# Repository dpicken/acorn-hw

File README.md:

# acorn-hw

Hardware for Acorn RISC OS computers.

- [A3010 SysClk Switcher](/doc/a3010-sysclk-switcher.md)

- [A3010 4 MiB RAM Upgrade](/doc/a3010-ram-upgrade.md)

- [Acorn USB Mouse](/doc/usb-mouse.md)

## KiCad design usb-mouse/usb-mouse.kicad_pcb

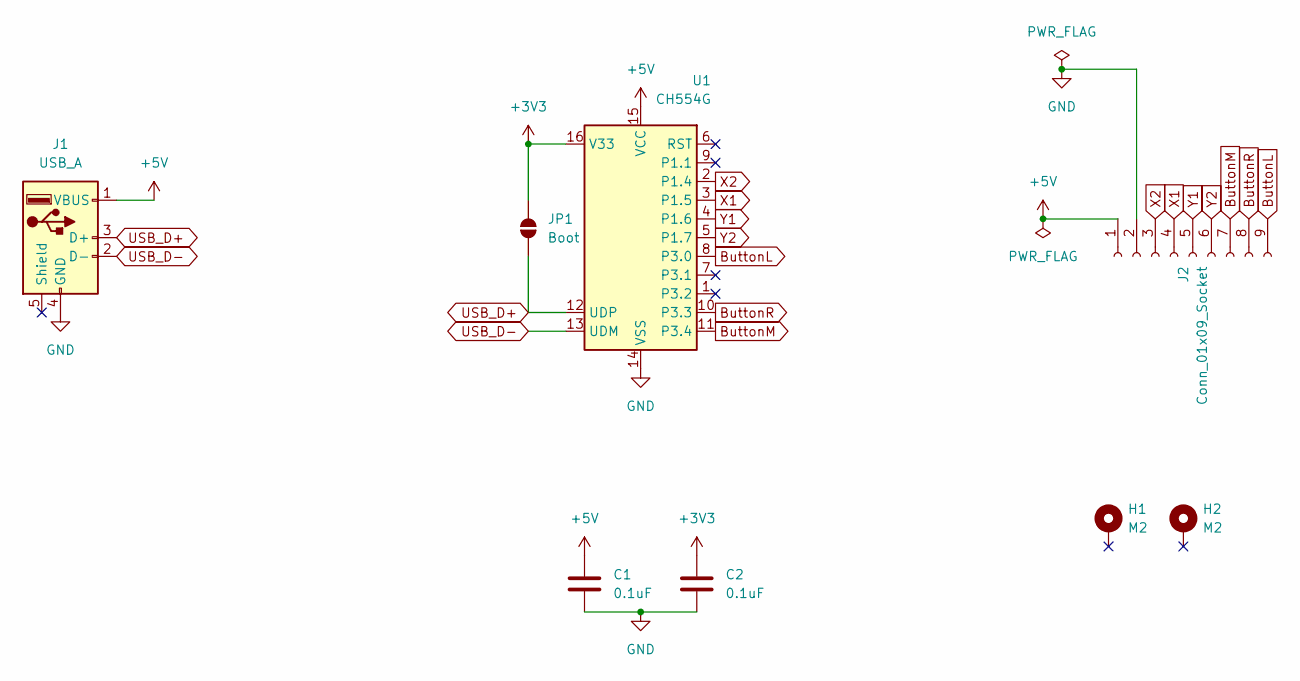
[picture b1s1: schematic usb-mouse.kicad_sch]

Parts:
C1, C2: 0.1uF; C_0805_2012Metric_Pad1.18x1.45mm_HandSolder
H1, H2: M2; MountingHole_2.2mm_M2_DIN965_Pad
J1: USB_A; USB_A_Molex_67643_Horizontal
J2: Conn_01x09_Socket; PinHeader_1x09_P1.27mm_Vertical
JP1: Boot; SolderJumper-2_P1.3mm_Open_RoundedPad1.0x1.5mm
U1: CH554G; STC_SOP-16_3.9x9.9mm_P1.27mm

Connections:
+3V3: C2.1, JP1.1 (A), U1.16 (V33)
+5V: C1.1, J1.1 (VBUS), J2.1, U1.15 (VCC)
ButtonL: J2.9, U1.8 (P3.0)
ButtonM: J2.7, U1.11 (P3.4)
ButtonR: J2.8, U1.10 (P3.3)
GND: C1.2, C2.2, J1.4 (GND), J2.2, U1.14 (VSS)
USB_D+: J1.3 (D+), JP1.2 (B), U1.12 (UDP)
USB_D-: J1.2 (D-), U1.13 (UDM)
X1: J2.4, U1.3 (P1.5)
X2: J2.3, U1.2 (P1.4)
Y1: J2.5, U1.4 (P1.6)
Y2: J2.6, U1.5 (P1.7)

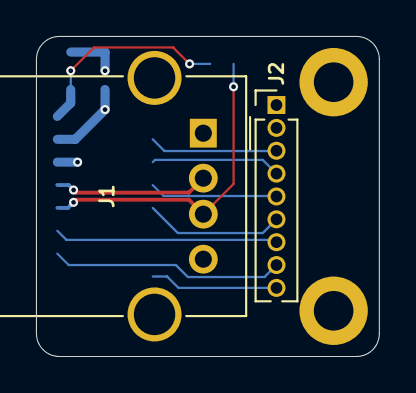
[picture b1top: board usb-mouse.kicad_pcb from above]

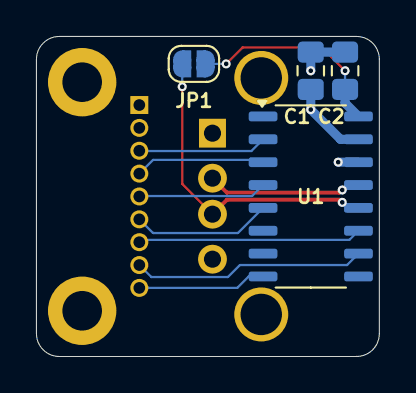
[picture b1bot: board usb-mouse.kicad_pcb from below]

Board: 4 copper layers, 19.1 x 17.8 mm, 8 parts (4 on the bottom side), 12 nets.

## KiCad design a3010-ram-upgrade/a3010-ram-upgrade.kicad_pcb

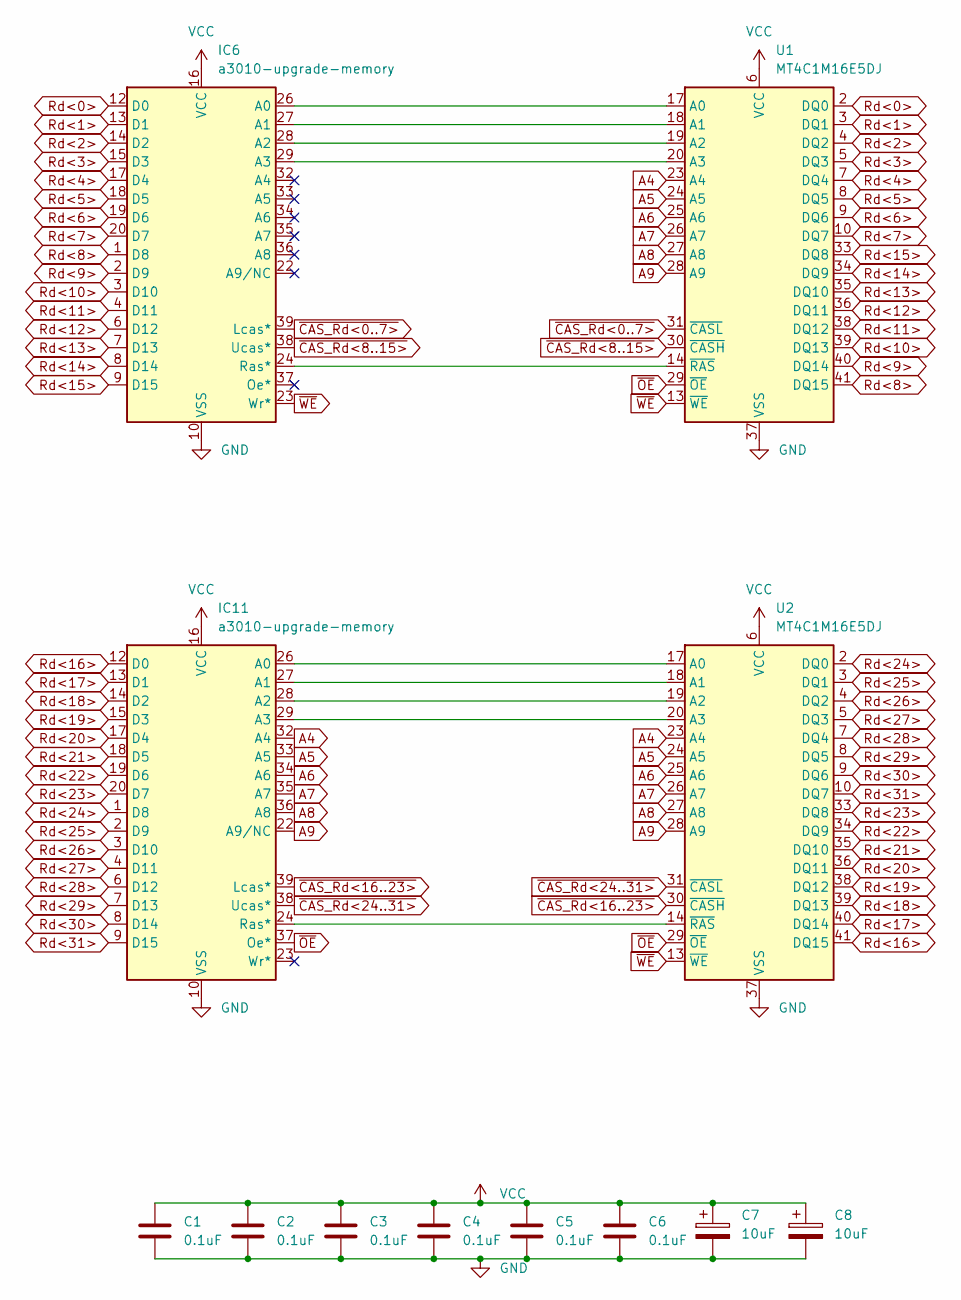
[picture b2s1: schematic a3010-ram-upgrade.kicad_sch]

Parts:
C1, C2, C3, C4, C5, C6: 0.1uF; C_0805_2012Metric_Pad1.18x1.45mm_HandSolder
C7, C8: 10uF; CP_EIA-2012-12_Kemet-R_HandSolder
IC6, IC11: a3010-upgrade-memory; zip-40
U1, U2: MT4C1M16E5DJ; SOJ-42_10.16x26.035mm_P1.27mm

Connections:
A4: IC11.32 (A4), U1.23 (A4), U2.23 (A4)
A5: IC11.33 (A5), U1.24 (A5), U2.24 (A5)
A6: IC11.34 (A6), U1.25 (A6), U2.25 (A6)
A7: IC11.35 (A7), U1.26 (A7), U2.26 (A7)
A8: IC11.36 (A8), U1.27 (A8), U2.27 (A8)
A9: IC11.22 (A9/NC), U1.28 (A9), U2.28 (A9)
GND: C1.2, C2.2, C3.2, C4.2, C5.2, C6.2, C7.2, C8.2, IC6.5 (VSS), IC6.10 (VSS), IC6.31 (VSS), IC11.5 (VSS), IC11.10 (VSS), IC11.31 (VSS), U1.22 (VSS), U1.37 (VSS), U1.42 (VSS), U2.22 (VSS), U2.37 (VSS), U2.42 (VSS)
unnamed: IC6.26 (A0), U1.17 (A0)
unnamed: IC6.27 (A1), U1.18 (A1)
unnamed: IC6.28 (A2), U1.19 (A2)
unnamed: IC6.29 (A3), U1.20 (A3)
unnamed: IC6.24 (Ras*), U1.14 (~RAS)
unnamed: IC11.26 (A0), U2.17 (A0)
unnamed: IC11.27 (A1), U2.18 (A1)
unnamed: IC11.28 (A2), U2.19 (A2)
unnamed: IC11.29 (A3), U2.20 (A3)
unnamed: IC11.24 (Ras*), U2.14 (~RAS)
Rd<0>: IC6.12 (D0), U1.2 (DQ0)
Rd<1>: IC6.13 (D1), U1.3 (DQ1)
Rd<2>: IC6.14 (D2), U1.4 (DQ2)
Rd<3>: IC6.15 (D3), U1.5 (DQ3)
Rd<4>: IC6.17 (D4), U1.7 (DQ4)
Rd<5>: IC6.18 (D5), U1.8 (DQ5)
Rd<6>: IC6.19 (D6), U1.9 (DQ6)
Rd<7>: IC6.20 (D7), U1.10 (DQ7)
Rd<8>: IC6.1 (D8), U1.41 (DQ15)
Rd<9>: IC6.2 (D9), U1.40 (DQ14)
Rd<10>: IC6.3 (D10), U1.39 (DQ13)
Rd<11>: IC6.4 (D11), U1.38 (DQ12)
Rd<12>: IC6.6 (D12), U1.36 (DQ11)
Rd<13>: IC6.7 (D13), U1.35 (DQ10)
Rd<14>: IC6.8 (D14), U1.34 (DQ9)
Rd<15>: IC6.9 (D15), U1.33 (DQ8)
Rd<16>: IC11.12 (D0), U2.41 (DQ15)
Rd<17>: IC11.13 (D1), U2.40 (DQ14)
Rd<18>: IC11.14 (D2), U2.39 (DQ13)
Rd<19>: IC11.15 (D3), U2.38 (DQ12)
Rd<20>: IC11.17 (D4), U2.36 (DQ11)
Rd<21>: IC11.18 (D5), U2.35 (DQ10)
Rd<22>: IC11.19 (D6), U2.34 (DQ9)
Rd<23>: IC11.20 (D7), U2.33 (DQ8)
Rd<24>: IC11.1 (D8), U2.2 (DQ0)
Rd<25>: IC11.2 (D9), U2.3 (DQ1)
Rd<26>: IC11.3 (D10), U2.4 (DQ2)
Rd<27>: IC11.4 (D11), U2.5 (DQ3)
Rd<28>: IC11.6 (D12), U2.7 (DQ4)
Rd<29>: IC11.7 (D13), U2.8 (DQ5)
Rd<30>: IC11.8 (D14), U2.9 (DQ6)
Rd<31>: IC11.9 (D15), U2.10 (DQ7)
VCC: C1.1, C2.1, C3.1, C4.1, C5.1, C6.1, C7.1, C8.1, IC6.11 (VCC), IC6.16 (VCC), IC6.30 (VCC), IC11.11 (VCC), IC11.16 (VCC), IC11.30 (VCC), U1.1 (VCC), U1.6 (VCC), U1.21 (VCC), U2.1 (VCC), U2.6 (VCC), U2.21 (VCC)
~CAS_Rd<0..7>: IC6.39 (Lcas*), U1.31 (~CASL)
~CAS_Rd<8..15>: IC6.38 (Ucas*), U1.30 (~CASH)
~CAS_Rd<16..23>: IC11.39 (Lcas*), U2.30 (~CASH)
~CAS_Rd<24..31>: IC11.38 (Ucas*), U2.31 (~CASL)
~OE: IC11.37 (Oe*), U1.29 (~OE), U2.29 (~OE)
~WE: IC6.23 (Wr*), U1.13 (~WE), U2.13 (~WE)

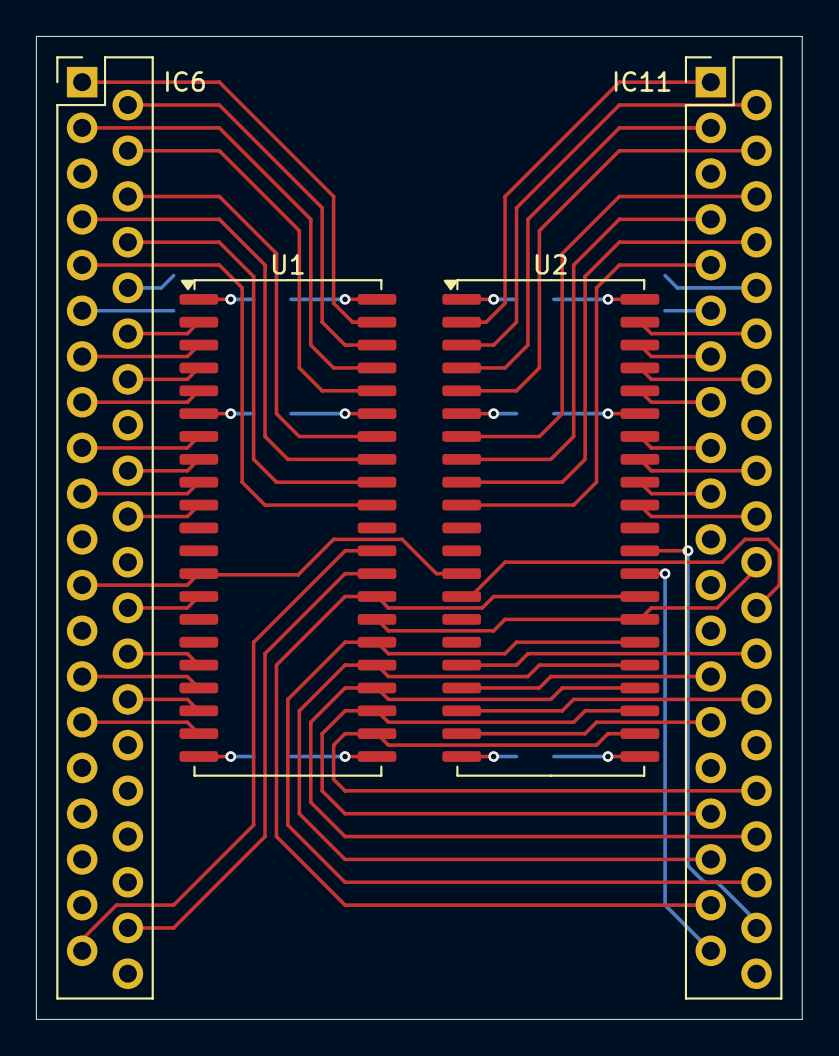
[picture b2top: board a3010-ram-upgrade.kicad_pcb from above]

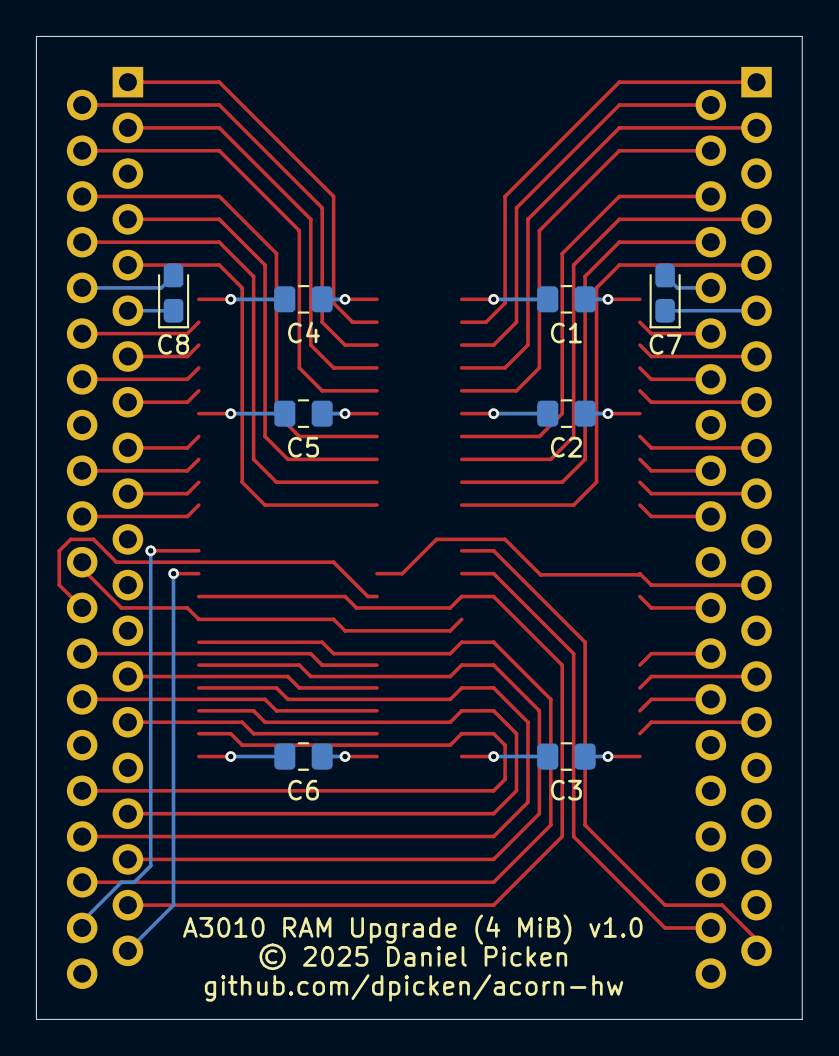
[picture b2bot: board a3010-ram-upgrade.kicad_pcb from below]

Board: 4 copper layers, 42.5 x 54.6 mm, 12 parts (8 on the bottom side), 56 nets.

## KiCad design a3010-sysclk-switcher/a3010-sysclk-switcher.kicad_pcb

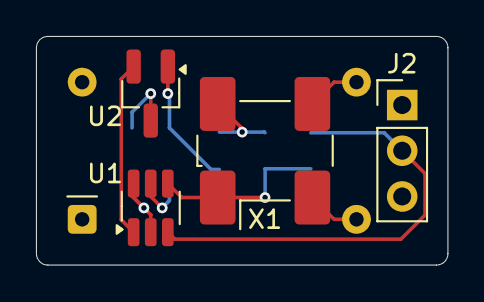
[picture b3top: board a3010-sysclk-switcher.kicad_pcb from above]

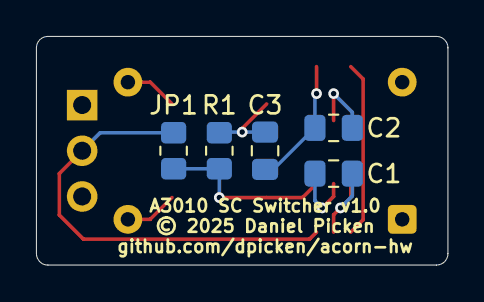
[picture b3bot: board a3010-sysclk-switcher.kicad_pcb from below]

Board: 4 copper layers, 22.9 x 12.7 mm, 10 parts (5 on the bottom side), 6 nets.

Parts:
C1, C2, C3: 0.1uF; C_0805_2012Metric_Pad1.18x1.45mm_HandSolder
J1: a3010-x3
J2: Conn_01x03_Pin; PinHeader_1x03_P2.54mm_Vertical
JP1: LATCH_BYPASS; R_0805_2012Metric_Pad1.20x1.40mm_HandSolder
R1: 1K; R_0805_2012Metric_Pad1.20x1.40mm_HandSolder
U1: 74LVC1G373; SOT-23-6_Handsoldering
U2: TLV810EA29DBZ; SOT-23_Handsoldering
X1: SG-8002CA; Oscillator_SMD_SeikoEpson_SG8002CA-4Pin_7.0x5.0mm_HandSolde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

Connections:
GND: C1.2, C2.2, C3.2, J1.7 (GND), J2.3, U1.2 (GND), U1.6 (~OE), U2.1 (GND), X1.2 (GND)
unnamed: J1.8 (sysclk), X1.3 (OUT)
unnamed: J2.2, JP1.1 (A), U1.3 (D)
unnamed: JP1.2 (B), R1.2, U1.4 (Q), X1.1 (OE)
unnamed: U1.1 (LE), U2.2 (RESET)
VCC: C1.1, C2.1, C3.1, J1.14 (Vcc), J2.1, R1.1, U1.5 (VCC), U2.3 (V_{DD}), X1.4 (Vcc)

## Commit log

2025-09-05 WIP: A3010 overclocking board
2025-09-22 A3010 overclocking board
2025-09-27 WIP: A3010 Ram upgrade
2025-10-02 A3010 4 MiB RAM upgrade
2026-06-17 USB mouse adapter

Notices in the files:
a3010-ram-upgrade/a3010-ram-upgrade.kicad_pcb:
© 2025 Daniel Picken
